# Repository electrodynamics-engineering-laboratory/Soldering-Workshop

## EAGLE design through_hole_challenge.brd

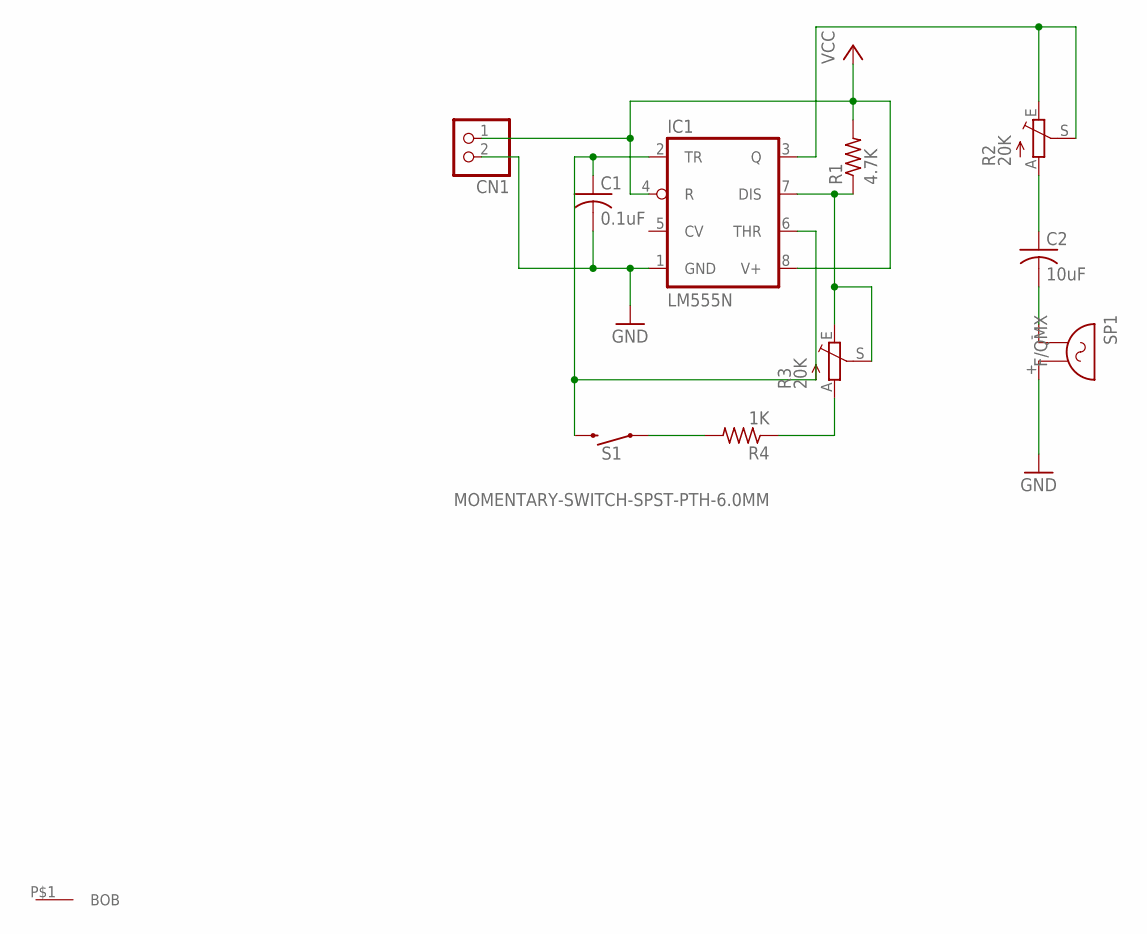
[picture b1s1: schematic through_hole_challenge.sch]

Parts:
C1: 0.1uF; C050-035X075
C2: 10uF; C050-035X075
CN1: JST_2PIN-THM-RA; JST-PH-2-THM-RA
IC1: LM555N; DIL08
R1: 4.7K; 0207/9
R2, R3: 20K; B25P
R4: 1K; 0207/9
S1: MOMENTARY-SWITCH-SPST-PTH-6.0MM; TACTILE_SWITCH_PTH_6.0MM
SP1: F/QMX
U$1: EEL_LOGO; BOB_LOGO

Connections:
GND: C1.2, CN1.2 (1), IC1.1 (GND), SP1.+ (2)
unnamed: C1.1, IC1.2 (TR), IC1.6 (THR), S1.3 (2)
unnamed: IC1.7 (DIS), R1.1, R3.E, R3.S
unnamed: R3.A, R4.1
unnamed: IC1.3 (Q), R2.E, R2.S
unnamed: C2.2, SP1.- (1)
unnamed: C2.1, R2.A
unnamed: R4.2, S1.1
VCC: CN1.1 (2), IC1.4 (R), IC1.8 (V+), R1.2

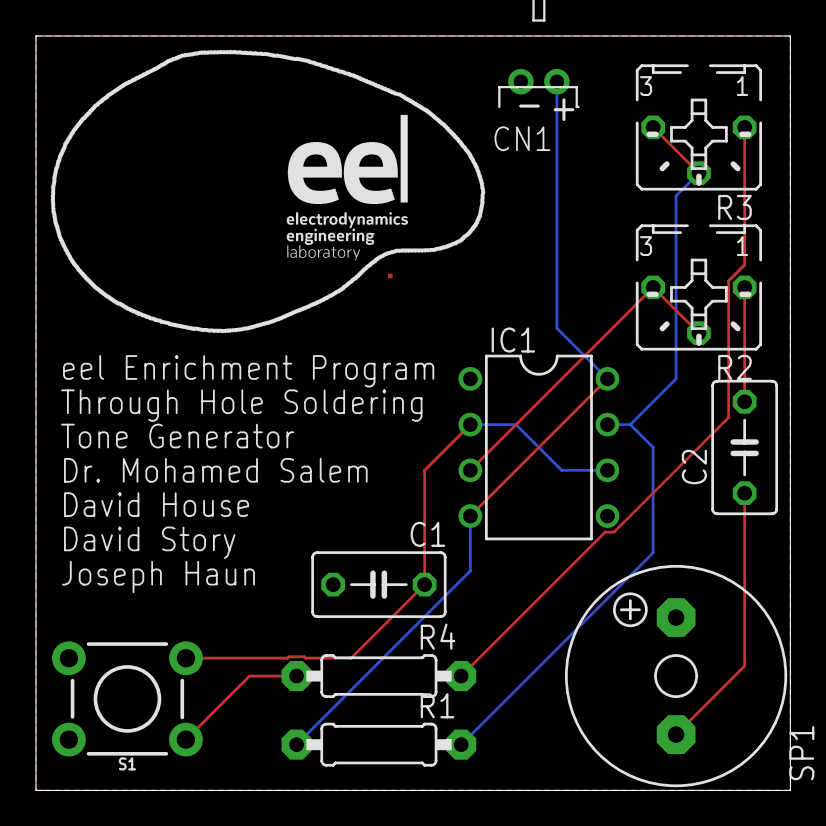
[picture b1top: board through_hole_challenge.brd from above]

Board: 2 copper layers, 41.9 x 41.9 mm, 11 parts (0 on the bottom side), 9 nets.

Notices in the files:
parts and their libraries:
SparkFun-Switches: Licensing: Creative Commons ShareAlike 4.0 International - https://creativecommons.org/licenses/by-sa/4.0
